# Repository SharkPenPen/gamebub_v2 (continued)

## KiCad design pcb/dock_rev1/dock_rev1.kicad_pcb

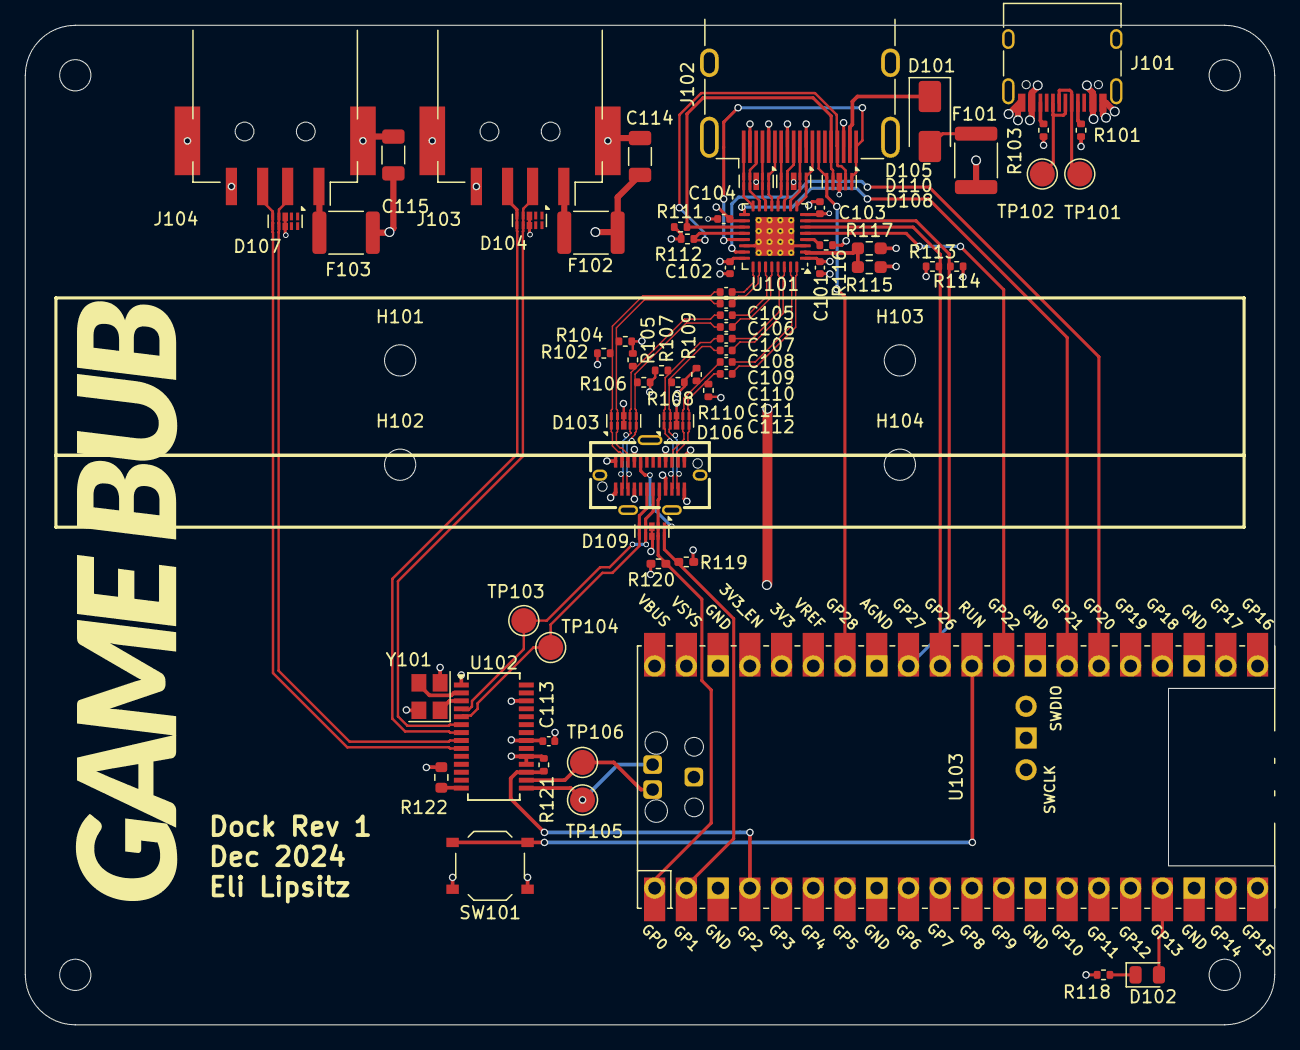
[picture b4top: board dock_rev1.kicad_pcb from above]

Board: 4 copper layers, 100.0 x 80.0 mm, 74 parts (0 on the bottom side), 63 nets.

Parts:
C101, C102, C103, C104, C105, C106, C107, C108, C109, C110, C111, C112, C113: 100n; C_0402_1005Metric
C114, C115: 100u; C_1206_3216Metric
D101: D_Schottky; D_SMA
D102: Green; LED_0805_2012Metric
D103, D104, D105, D106, D107, D108, D109, D110: H5VU25U; Diodes_UDFN-10_1.0x2.5mm_P0.5mm
F101, F102, F103: 500mA; Fuse_1812_4532Metric
H101, H102, H103, H104, H105, H106, H107, H108: MountingHole; MountingHole_2.5mm
J101: USB_C_Receptacle_USB2.0_16P; USB_C_Receptacle_HRO_TYPE-C-31-M-12
J102: HDMI_A; HDMI_A_Molex_208658-1001_Horizontal
J103, J104: USB_A; USB_A_Receptacle_Xunpu_USB-234-BCW
P101: USB_C_Plug; USB-C-SMD_TYPEC-952-ACP24
R101, R103: 5K1; R_0402_1005Metric
R102, R104, R105, R106, R107, R108, R109, R110: 49R9; R_0402_1005Metric
R111, R112, R113, R114, R118: 2K; R_0402_1005Metric
R115, R117: 0R; R_0603_1608Metric_Pad0.98x0.95mm_HandSolder
R116, R121: 10K; R_0402_1005Metric
R119, R120: 2K; R_0402_1005Metric_Pad0.72x0.64mm_HandSolder
R122: 2K7; R_0603_1608Metric
SW101: SW_Push; SW_Push_1P1T_XKB_TS-1187A
TP101, TP102, TP103, TP104, TP105, TP106: TestPoint; TestPoint_Pad_D2.0mm
U101: PTN3365; HVQFN-32-1EP_5x5mm_P0.5mm_EP3.1x3.1mm_ThermalVias
U102: FE1.1s; SSOP-28_3.9x9.9mm_P0.635mm
U103: PicoW; RPi_PicoW_SMD_TH
Y101: 12MHz; Crystal_SMD_3225-4Pin_3.2x2.5mm

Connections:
+3V3: C101.1, C102.1, C103.1, C104.1, C113.1, R102.1, R104.1, R105.1, R106.1, R107.1, R108.1, R109.1, R110.1, R111.1, R112.1, R113.1, R114.1, R115.1, R119.2, R120.2, R121.1, U101.1 (VDD), U101.8 (VDD), U101.18 (VDD), U101.24 (VDD), U102.18 (VBUSM), U102.19 (BUSJ), U102.21 (VD33F), U102.26 (OVCJ), U103.36 (3V3)
/HDMI_+5V_F: D101.2 (A), F101.2
/HDMI_C_CLK+: C111.2, U101.31 (IN_D4−)
/HDMI_C_CLK-: C112.2, U101.32 (IN_D4+)
/HDMI_C_D0+: C109.2, U101.29 (IN_D3−)
/HDMI_C_D0-: C110.2, U101.30 (IN_D3+)
/HDMI_C_D1+: C107.2, U101.27 (IN_D2−)
/HDMI_C_D1-: C108.2, U101.28 (IN_D2+)
/HDMI_C_D2+: C105.2, U101.25 (IN_D1−)
/HDMI_C_D2-: C106.2, U101.26 (IN_D1+)
/HDMI_DDC_EN: U101.23 (DDC_EN), U103.26 (GPIO20)
/HDMI_EQ5: R115.2, R117.1, U101.2 (EQ5)
/HDMI_HPD: U101.5 (HPD_SOURCE), U103.29 (GPIO22)
/HDMI_OUT_+5V: D101.1 (K), J102.18 (+5V)
/HDMI_OUT_CEC: D110.5 (K4), D110.6 (K4), J102.13 (CEC), U103.34 (GPIO28_ADC2)
/HDMI_OUT_CLK+: D108.2 (K2), D108.9 (K2), J102.10 (CK+), U101.10 (OUT_D4−)
/HDMI_OUT_CLK-: D108.1 (K1), D108.10 (K1), J102.12 (CK-), U101.9 (OUT_D4+)
/HDMI_OUT_D0+: D108.5 (K4), D108.6 (K4), J102.7 (D0+), U101.12 (OUT_D3−)
/HDMI_OUT_D0-: D108.4 (K3), D108.7 (K3), J102.9 (D0-), U101.11 (OUT_D3+)
/HDMI_OUT_D1+: D105.2 (K2), D105.9 (K2), J102.4 (D1+), U101.14 (OUT_D2−)
/HDMI_OUT_D1-: D105.1 (K1), D105.10 (K1), J102.6 (D1-), U101.13 (OUT_D2+)
/HDMI_OUT_D2+: D105.5 (K4), D105.6 (K4), J102.1 (D2+), U101.16 (OUT_D1−)
/HDMI_OUT_D2-: D105.4 (K3), D105.7 (K3), J102.3 (D2-), U101.15 (OUT_D1+)
/HDMI_OUT_HPD: D110.1 (K1), D110.10 (K1), J102.19 (HPD), U101.21 (HPD_SINK)
/HDMI_OUT_SCL: D110.4 (K3), D110.7 (K3), J102.15 (SCL), R111.2, U101.19 (SCL_SINK)
/HDMI_OUT_SDA: D110.2 (K2), D110.9 (K2), J102.16 (SDA), R112.2, U101.20 (SDA_SINK)
/HDMI_REXT: R116.2, U101.4 (REXT)
/HDMI_SCL: R114.2, U101.7 (SCL_SOURCE), U103.32 (GPIO27_ADC1)
/HDMI_SDA: R113.2, U101.6 (SDA_SOURCE), U103.31 (GPIO26_ADC0)
/HDMI_TX_CLK+: C111.1, D106.4 (K3), D106.7 (K3), P101.B3 (TX2-), R109.2
/HDMI_TX_CLK-: C112.1, D106.5 (K4), D106.6 (K4), P101.B2 (TX2+), R110.2
/HDMI_TX_D0+: C109.1, D106.1 (K1), D106.10 (K1), P101.A10 (RX2-), R107.2
/HDMI_TX_D0-: C110.1, D106.2 (K2), D106.9 (K2), P101.A11 (RX2+), R108.2
/HDMI_TX_D1+: C107.1, D103.4 (K3), D103.7 (K3), P101.A2 (TX1+), R105.2
/HDMI_TX_D1-: C108.1, D103.5 (K4), D103.6 (K4), P101.A3 (TX1-), R106.2
/HDMI_TX_D2+: C105.1, D103.1 (K1), D103.10 (K1), P101.B11 (RX1+), R102.2
/HDMI_TX_D2-: C106.1, D103.2 (K2), D103.9 (K2), P101.B10 (RX1-), R104.2
/HDMI_~OE: U101.17 (~OE), U103.27 (GPIO21)
/LED: D102.2 (A), U103.17 (GPIO13)
/LED_K: D102.1 (K), R118.1
/MCU_RUN: SW101.2, U103.30 (RUN)
/MCU_USB_D+: TP106.1, U102.16 (DPU), U103.TP3 (USB_D+)
/MCU_USB_D-: TP105.1, U102.15 (DMU), U103.TP2 (USB_D-)
/USB_Device1_D+: D107.5 (K4), D107.6 (K4), J104.3 (D+), U102.9 (DP2)
/USB_Device1_D-: D107.4 (K3), D107.7 (K3), J104.2 (D-), U102.8 (DM2)
/USB_Device2_D+: D104.5 (K4), D104.6 (K4), J103.3 (D+), U102.7 (DP3)
/USB_Device2_D-: D104.4 (K3), D104.7 (K3), J103.2 (D-), U102.6 (DM3)
/USB_Handheld_D+: D109.5 (K4), D109.6 (K4), P101.A6 (D+), TP104.1, U102.5 (DP4)
/USB_Handheld_D-: D109.4 (K3), D109.7 (K3), P101.A7 (D-), TP103.1, U102.4 (DM4)
/USB_Handheld_SBU1: D109.2 (K2), D109.9 (K2), P101.A8 (SBU1), R120.1, U103.1 (GPIO0)
/USB_Handheld_SBU2: D109.1 (K1), D109.10 (K1), P101.B8 (SBU2), R119.1, U103.2 (GPIO1)
/USB_Hub_Rext: R122.2, U102.14 (REXT)
/USB_Hub_XIn: U102.3 (XIN), Y101.1
/USB_Hub_XOut: U102.2 (XOUT), Y101.3
/USB_Power_CC1: J101.A5 (CC1), R101.2
/USB_Power_CC2: J101.B5 (CC2), R103.2
/USB_Power_D+: J101.A6 (D+), J101.B6 (D+), TP102.1
/USB_Power_D-: J101.A7 (D-), J101.B7 (D-), TP101.1
/~USB_Hub_RST: R121.2, U102.17 (~XRSTJ), U103.4 (GPIO2)
GND: C101.2, C102.2, C103.2, C104.2, C113.2, C114.2, C115.2, D103.3 (A), D103.8 (A), D104.3 (A), D104.8 (A), D105.3 (A), D105.8 (A), D106.3 (A), D106.8 (A), D107.3 (A), D107.8 (A), D108.3 (A), D108.8 (A), D109.3 (A), D109.8 (A), D110.3 (A), D110.8 (A), J101.A1 (GND), J101.A12 (GND), J101.B1 (GND), J101.B12 (GND), J101.S1 (SHIELD), J102.2 (D2S), J102.5 (D1S), J102.8 (D0S), J102.11 (CKS), J102.17 (GND), J102.SH, J103.4 (GND), J103.5 (Shield), J104.4 (GND), J104.5 (Shield), P101.A1 (GND), P101.A12 (GND), P101.B1 (GND), P101.B12 (GND), P101.S1 (SHIELD), R101.1, R103.1, R116.1, R117.2, R118.2, R122.1, SW101.1, U101.3 (TEST), U101.22 (GND), U101.33 (GND), U102.1 (VSS), U103.3 (GND), U103.8 (GND), U103.13 (GND), U103.18 (GND), U103.23 (GND), U103.28 (GND), U103.33 (AGND), U103.38 (GND), U103.42 (GND), U103.TP1 (GND), Y101.2, Y101.4
unnamed: F102.1, J103.1 (VBUS)
unnamed: F103.1, J104.1 (VBUS)
VBUS: C114.1, C115.1, F101.1, F102.2, F103.2, J101.A4 (VBUS), J101.A9 (VBUS), J101.B4 (VBUS), J101.B9 (VBUS), P101.A4 (VBUS), P101.A9 (VBUS), P101.B4 (VBUS), P101.B9 (VBUS), U103.39 (VSYS), U103.40 (VBUS)

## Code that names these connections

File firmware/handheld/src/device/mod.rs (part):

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    button_vol_down: PinDriver<'a, AnyInputPin, Input>,
    button_power: PinDriver<'a, AnyIOPin, InputOutput>,
    pin_irq: PinDriver<'a, AnyInputPin, Input>,
    pin_vbus_pgood: PinDriver<'a, AnyIOPin, Input>,
    pin_batt_chg: PinDriver<'a, AnyInputPin, Input>,

    /// Sdcard,
    pub sdcard: Option<Sdcard>,
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        let peripherals = Peripherals::take()?;
        cfg_if::cfg_if! {
            if #[cfg(feature = "rev2")] {
                let pin_led = peripherals.pins.gpio36.downgrade_output();
                let pin_irq = peripherals.pins.gpio16.downgrade_input();
                let pin_home = peripherals.pins.gpio0.downgrade_input();
                let pin_vol_up = peripherals.pins.gpio41.downgrade_input();
                let pin_vol_down = peripherals.pins.gpio40.downgrade_input();
                let pin_power_switch = peripherals.pins.gpio15.downgrade();
                let pin_vbus_pgood = peripherals.pins.gpio17.downgrade();
                let pin_batt_chg = peripherals.pins.gpio39.downgrade_input();
                let pin_lcd_backlight = peripherals.pins.gpio42.downgrade_output();
                let pin_lcd_reset = peripherals.pins.gpio1.downgrade_output();
                let pin_lcd_cs = peripherals.pins.gpio2.downgrade_output();
                let pin_lcd_dc = peripherals.pins.gpio3.downgrade_output();
                let pin_lcd_spi_clk = peripherals.pins.gpio4.downgrade_output();
                let pin_lcd_spi_d0 = peripherals.pins.gpio5.downgrade_output();
                let pin_fpga_power = peripherals.pins.gpio46.downgrade_output();
                let pin_fpga_init_b = peripherals.pins.gpio8.downgrade();
                let pin_fpga_done = peripherals.pins.gpio6.downgrade_input();
                let pin_fpga_program_b = peripherals.pins.gpio7.downgrade_output();
                let mut pin_fpga_spi_cs = peripherals.pins.gpio10.downgrade_output();
                let pin_fpga_spi_clk = peripherals.pins.gpio12.downgrade_output();
                let pin_fpga_spi_d0 = peripherals.pins.gpio11.downgrade();
                let pin_fpga_spi_d1 = peripherals.pins.gpio13.downgrade();
                let pin_fpga_spi_d2 = peripherals.pins.gpio14.downgrade();
                let pin_fpga_spi_d3 = peripherals.pins.gpio9.downgrade();
                let pin_i2c_scl = peripherals.pins.gpio37.downgrade();
                let pin_i2c_sda = peripherals.pins.gpio38.downgrade();
                let pin_sdio_clk = peripherals.pins.gpio33.downgrade_output();
                let pin_sdio_cmd = peripherals.pins.gpio47.downgrade();
                let pin_sdio_d0 = peripherals.pins.gpio34.downgrade();
                let pin_sdio_d1 = peripherals.pins.gpio48.downgrade();
                let pin_sdio_d2 = peripherals.pins.gpio21.downgrade();
                let pin_sdio_d3 = peripherals.pins.gpio26.downgrade();
                let pin_sd_detect = peripherals.pins.gpio35.downgrade_input();
                let pin_dac_reset = peripherals.pins.gpio45.downgrade_output();
            }
        }

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                    .frequency(25.kHz().into())
                    .resolution(ledc::config::Resolution::Bits11),
            )?,
            pin_lcd_backlight,
        )?;
        lcd_backlight.set_duty_cycle_fully_off().unwrap();

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            if #[cfg(feature = "rev2")] {
                let fpga_spi_driver = &*Box::leak(Box::new(SpiDriver::new_quad(
                    peripherals.spi2,
                    pin_fpga_spi_clk,
                    pin_fpga_spi_d0,
                    pin_fpga_spi_d1,
                    pin_fpga_spi_d2,
                    pin_fpga_spi_d3,
                    &spi_driver_config,
                )?));
                let lcd_spi_driver = &*Box::leak(Box::new(SpiDriver::new(
                    peripherals.spi3,
                    pin_lcd_spi_clk,
                    pin_lcd_spi_d0,
                    Option::<AnyInputPin>::None,
                    &spi_driver_config,
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        let lcd_spi_config = spi::config::Config::new().baudrate(10.MHz().into());
        let lcd_spi = SpiSoftCsDeviceDriver::new(
            SpiSharedDeviceDriver::new(lcd_spi_driver, &lcd_spi_config)?,
            pin_lcd_cs,
            gpio::Level::High,
        )?;
        let lcd_reset = PinDriver::output(pin_lcd_reset)?;
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        // Setup battery fuel gauge
        let mut fuel_gauge = drivers::fuel_gauge::MAX17048::new(MutexI2C::new(&i2c));
        let _ = fuel_gauge.set_alert_soc_change(true); // fuel gauge won't work without a battery
        let mut pin_vbus_pgood = PinDriver::input(pin_vbus_pgood)?;
        pin_vbus_pgood.set_pull(gpio::Pull::Up)?;
        let pin_batt_chg = PinDriver::input(pin_batt_chg)?;

        // Low-voltage interlock: never bring the FPGA up on a collapsing rail.
        // The FPGA is simply left unpowered and the boot continues, so the
        // self-test can still report why the device is not starting.
        let vbus_present = pin_vbus_pgood.is_low(); // Active low
        match fuel_gauge.get_battery_voltage() {
            Ok(voltage) if crate::power::is_battery_critical(voltage, vbus_present) => {
                log::error!(
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
        // Setup DAC (requires fpga_power on)
        log::info!("Initializing DAC");
        let dac_reset = PinDriver::output(pin_dac_reset)?;
        let mut dac = drivers::dac::TLV320DAC3101::new(dac_reset, MutexI2C::new(&i2c));
        // The DAC shares the I2C bus and sits on the FPGA power domain, so a
        // failure here must not stop the boot.
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        }

        // Setup FPGA (without programming)
        let fpga_done = PinDriver::input(pin_fpga_done)?;
        let mut fpga_program_b = PinDriver::output_od(pin_fpga_program_b)?;
        fpga_program_b.set_high()?; // Initializing pin sets this to low -- release it to high-z immediately.
        let fpga_init_b = PinDriver::input(pin_fpga_init_b)?;

        let spi_rates = [40.MHz(), 20.MHz(), 16.MHz(), 10.MHz()];
        let fpga_data_spis = spi_rates
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                // They're used in the same mode (output), and controlled only by software,
                // and never used at the same time (either read *or* write are used at any time).
                // There doesn't appear to be any other way to use multiple clock speeds.
                let cs_pin = unsafe { pin_fpga_spi_cs.clone_unchecked() };
                let mut spi = SpiSoftCsDeviceDriver::new(
                    SpiSharedDeviceDriver::new(fpga_spi_driver, &config).unwrap(),
                    cs_pin,
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        // Mount sdcard to /sdcard
        let sdcard = drivers::sdcard::mount_sdcard(
            "/sdcard",
            pin_sdio_clk,
            pin_sdio_cmd,
            pin_sdio_d0,
            pin_sdio_d1,
            pin_sdio_d2,
            pin_sdio_d3,
            Some(pin_sd_detect),
        )
        .ok();

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            button_vol_up,
            button_vol_down,
            pin_irq,
            pin_batt_chg,
            pin_vbus_pgood,
            rtc,
            imu,
            sdcard,
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    }

    pub fn get_battery_is_charging(&self) -> bool {
        self.pin_batt_chg.is_high()
    }

    pub fn get_vbus_pgood(&self) -> bool {
        self.pin_vbus_pgood.is_low() // Active low
    }
}

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
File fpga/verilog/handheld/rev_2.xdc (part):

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########################################
# Link Port
########################################
set_property -dict { PACKAGE_PIN C1     IOSTANDARD LVCMOS33 } [get_ports { link_so     }];
set_property -dict { PACKAGE_PIN D2     IOSTANDARD LVCMOS33 } [get_ports { link_si     }];
set_property -dict { PACKAGE_PIN E2     IOSTANDARD LVCMOS33 } [get_ports { link_sd     }];
set_property -dict { PACKAGE_PIN G2     IOSTANDARD LVCMOS33 } [get_ports { link_sc     }];
set_property -dict { PACKAGE_PIN C2     IOSTANDARD LVCMOS33 } [get_ports { link_so_dir }];
set_property -dict { PACKAGE_PIN E1     IOSTANDARD LVCMOS33 } [get_ports { link_si_dir }];
set_property -dict { PACKAGE_PIN F1     IOSTANDARD LVCMOS33 } [get_ports { link_sd_dir }];
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########################################
# LCD
########################################
set_property -dict { PACKAGE_PIN E17    IOSTANDARD LVCMOS33 } [get_ports { lcd_dotclk  }];
set_property -dict { PACKAGE_PIN E18    IOSTANDARD LVCMOS33 } [get_ports { lcd_hsync   }];
set_property -dict { PACKAGE_PIN D17    IOSTANDARD LVCMOS33 } [get_ports { lcd_vsync   }];
set_property -dict { PACKAGE_PIN F18    IOSTANDARD LVCMOS33 } [get_ports { lcd_data_en }];
set_property -dict { PACKAGE_PIN T11    IOSTANDARD LVCMOS33 } [get_ports { lcd_te      }];
set_property -dict { PACKAGE_PIN K16    IOSTANDARD LVCMOS33 } [get_ports { lcd_db[0]   }];
set_property -dict { PACKAGE_PIN K15    IOSTANDARD LVCMOS33 } [get_ports { lcd_db[1]   }];
set_property -dict { PACKAGE_PIN J15    IOSTANDARD LVCMOS33 } [get_ports { lcd_db[2]   }];
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########################################
# Buttons
########################################
set_property -dict { PACKAGE_PIN N5     IOSTANDARD LVCMOS33 } [get_ports { btn_a      }];
set_property -dict { PACKAGE_PIN P5     IOSTANDARD LVCMOS33 } [get_ports { btn_b      }];
set_property -dict { PACKAGE_PIN L6     IOSTANDARD LVCMOS33 } [get_ports { btn_x      }];
set_property -dict { PACKAGE_PIN M6     IOSTANDARD LVCMOS33 } [get_ports { btn_y      }];
set_property -dict { PACKAGE_PIN E5     IOSTANDARD LVCMOS33 } [get_ports { btn_up     }];
set_property -dict { PACKAGE_PIN H5     IOSTANDARD LVCMOS33 } [get_ports { btn_down   }];
set_property -dict { PACKAGE_PIN G6     IOSTANDARD LVCMOS33 } [get_ports { btn_left   }];
set_property -dict { PACKAGE_PIN F5     IOSTANDARD LVCMOS33 } [get_ports { btn_right  }];
set_property -dict { PACKAGE_PIN E6     IOSTANDARD LVCMOS33 } [get_ports { btn_l      }];
set_property -dict { PACKAGE_PIN L5     IOSTANDARD LVCMOS33 } [get_ports { btn_r      }];
set_property -dict { PACKAGE_PIN K5     IOSTANDARD LVCMOS33 } [get_ports { btn_start  }];
set_property -dict { PACKAGE_PIN J5     IOSTANDARD LVCMOS33 } [get_ports { btn_select }];

########################################
# DAC I2S
########################################
set_property -dict { PACKAGE_PIN G4     IOSTANDARD LVCMOS33 } [get_ports { dac_mclk }];
set_property -dict { PACKAGE_PIN H4     IOSTANDARD LVCMOS33 } [get_ports { dac_wclk }];
set_property -dict { PACKAGE_PIN G3     IOSTANDARD LVCMOS33 } [get_ports { dac_bclk }];
set_property -dict { PACKAGE_PIN J4     IOSTANDARD LVCMOS33 } [get_ports { dac_din  }];

########################################
# MCU Communication
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set_property -dict { PACKAGE_PIN A18    IOSTANDARD TMDS_33  } [get_ports { hdmi_data_p[2] }];
set_property -dict { PACKAGE_PIN B18    IOSTANDARD TMDS_33  } [get_ports { hdmi_data_n[2] }];

set_property -dict { PACKAGE_PIN F3     IOSTANDARD LVCMOS33 } [get_ports { usb_sbu_1 }];
set_property -dict { PACKAGE_PIN D3     IOSTANDARD LVCMOS33 } [get_ports { usb_sbu_2 }];

########################################
# Vibration
########################################
set_property -dict { PACKAGE_PIN B1     IOSTANDARD LVCMOS33 } [get_ports { vibrate_en    }];
set_property -dict { PACKAGE_PIN A1     IOSTANDARD LVCMOS33 } [get_ports { vibrate_brake }];

########################################
# PMOD
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set_property -dict { PACKAGE_PIN N4     IOSTANDARD LVCMOS33 } [get_ports { sdram_bs[0] }];
set_property -dict { PACKAGE_PIN P3     IOSTANDARD LVCMOS33 } [get_ports { sdram_bs[1] }];

set_property -dict { PACKAGE_PIN V4     IOSTANDARD LVCMOS33 } [get_ports { sdram_clk   }];
set_property -dict { PACKAGE_PIN R2     IOSTANDARD LVCMOS33 } [get_ports { sdram_we_n  }];
set_property -dict { PACKAGE_PIN R1     IOSTANDARD LVCMOS33 } [get_ports { sdram_ldqm  }];
set_property -dict { PACKAGE_PIN T5     IOSTANDARD LVCMOS33 } [get_ports { sdram_udqm  }];
set_property -dict { PACKAGE_PIN T1     IOSTANDARD LVCMOS33 } [get_ports { sdram_cas_n }];
set_property -dict { PACKAGE_PIN U1     IOSTANDARD LVCMOS33 } [get_ports { sdram_ras_n }];
set_property -dict { PACKAGE_PIN U4     IOSTANDARD LVCMOS33 } [get_ports { sdram_cke   }];
set_property -dict { PACKAGE_PIN V1     IOSTANDARD LVCMOS33 } [get_ports { sdram_cs_n  }];

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
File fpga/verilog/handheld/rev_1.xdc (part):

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########################################
# Link Port
########################################
set_property -dict { PACKAGE_PIN L13    IOSTANDARD LVCMOS33 } [get_ports { link_so     }];
set_property -dict { PACKAGE_PIN J14    IOSTANDARD LVCMOS33 } [get_ports { link_si     }];
set_property -dict { PACKAGE_PIN F14    IOSTANDARD LVCMOS33 } [get_ports { link_sd     }];
set_property -dict { PACKAGE_PIN G13    IOSTANDARD LVCMOS33 } [get_ports { link_sc     }];
set_property -dict { PACKAGE_PIN L14    IOSTANDARD LVCMOS33 } [get_ports { link_so_dir }];
set_property -dict { PACKAGE_PIN H14    IOSTANDARD LVCMOS33 } [get_ports { link_si_dir }];
set_property -dict { PACKAGE_PIN F13    IOSTANDARD LVCMOS33 } [get_ports { link_sd_dir }];
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########################################
# LCD
########################################
set_property -dict { PACKAGE_PIN E17    IOSTANDARD LVCMOS33 } [get_ports { lcd_dotclk  }];
set_property -dict { PACKAGE_PIN E18    IOSTANDARD LVCMOS33 } [get_ports { lcd_hsync   }];
set_property -dict { PACKAGE_PIN D17    IOSTANDARD LVCMOS33 } [get_ports { lcd_vsync   }];
set_property -dict { PACKAGE_PIN F18    IOSTANDARD LVCMOS33 } [get_ports { lcd_data_en }];
set_property -dict { PACKAGE_PIN K16    IOSTANDARD LVCMOS33 } [get_ports { lcd_db[0]   }];
set_property -dict { PACKAGE_PIN K15    IOSTANDARD LVCMOS33 } [get_ports { lcd_db[1]   }];
set_property -dict { PACKAGE_PIN J15    IOSTANDARD LVCMOS33 } [get_ports { lcd_db[2]   }];
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########################################
# Buttons
########################################
set_property -dict { PACKAGE_PIN N5     IOSTANDARD LVCMOS33 } [get_ports { btn_a      }];
set_property -dict { PACKAGE_PIN P5     IOSTANDARD LVCMOS33 } [get_ports { btn_b      }];
set_property -dict { PACKAGE_PIN L6     IOSTANDARD LVCMOS33 } [get_ports { btn_x      }];
set_property -dict { PACKAGE_PIN M6     IOSTANDARD LVCMOS33 } [get_ports { btn_y      }];
set_property -dict { PACKAGE_PIN E5     IOSTANDARD LVCMOS33 } [get_ports { btn_up     }];
set_property -dict { PACKAGE_PIN H5     IOSTANDARD LVCMOS33 } [get_ports { btn_down   }];
set_property -dict { PACKAGE_PIN G6     IOSTANDARD LVCMOS33 } [get_ports { btn_left   }];
set_property -dict { PACKAGE_PIN F5     IOSTANDARD LVCMOS33 } [get_ports { btn_right  }];
set_property -dict { PACKAGE_PIN H6     IOSTANDARD LVCMOS33 } [get_ports { btn_l      }];
set_property -dict { PACKAGE_PIN L5     IOSTANDARD LVCMOS33 } [get_ports { btn_r      }];
set_property -dict { PACKAGE_PIN K5     IOSTANDARD LVCMOS33 } [get_ports { btn_start  }];
set_property -dict { PACKAGE_PIN J5     IOSTANDARD LVCMOS33 } [get_ports { btn_select }];

########################################
# DAC I2S
########################################
set_property -dict { PACKAGE_PIN G4     IOSTANDARD LVCMOS33 } [get_ports { dac_mclk }];
set_property -dict { PACKAGE_PIN H4     IOSTANDARD LVCMOS33 } [get_ports { dac_wclk }];
set_property -dict { PACKAGE_PIN G3     IOSTANDARD LVCMOS33 } [get_ports { dac_bclk }];
set_property -dict { PACKAGE_PIN J4     IOSTANDARD LVCMOS33 } [get_ports { dac_din  }];

########################################
# MCU Communication
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set_property -dict { PACKAGE_PIN F1     IOSTANDARD TMDS_33  } [get_ports { hdmi_data_p[2] }];
set_property -dict { PACKAGE_PIN E1     IOSTANDARD TMDS_33  } [get_ports { hdmi_data_n[2] }];

# set_property -dict { PACKAGE_PIN D3     IOSTANDARD LVCMOS33 } [get_ports { hdmi_scl   }];
# set_property -dict { PACKAGE_PIN E6     IOSTANDARD LVCMOS33 } [get_ports { hdmi_sda   }];
# set_property -dict { PACKAGE_PIN F3     IOSTANDARD LVCMOS33 } [get_ports { hdmi_hpd_n }];
# set_property -dict { PACKAGE_PIN F6     IOSTANDARD LVCMOS33 } [get_ports { hdmi_cec   }];

########################################
# Vibration
########################################
set_property -dict { PACKAGE_PIN E7     IOSTANDARD LVCMOS33 } [get_ports { vibrate_en }];

########################################
# PMOD
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set_property -dict { PACKAGE_PIN N4     IOSTANDARD LVCMOS33 } [get_ports { sdram_bs[0] }];
set_property -dict { PACKAGE_PIN P3     IOSTANDARD LVCMOS33 } [get_ports { sdram_bs[1] }];

set_property -dict { PACKAGE_PIN V4     IOSTANDARD LVCMOS33 } [get_ports { sdram_clk   }];
set_property -dict { PACKAGE_PIN R2     IOSTANDARD LVCMOS33 } [get_ports { sdram_we_n  }];
set_property -dict { PACKAGE_PIN R1     IOSTANDARD LVCMOS33 } [get_ports { sdram_ldqm  }];
set_property -dict { PACKAGE_PIN T5     IOSTANDARD LVCMOS33 } [get_ports { sdram_udqm  }];
set_property -dict { PACKAGE_PIN T1     IOSTANDARD LVCMOS33 } [get_ports { sdram_cas_n }];
set_property -dict { PACKAGE_PIN U1     IOSTANDARD LVCMOS33 } [get_ports { sdram_ras_n }];
set_property -dict { PACKAGE_PIN U4     IOSTANDARD LVCMOS33 } [get_ports { sdram_cke   }];
set_property -dict { PACKAGE_PIN V1     IOSTANDARD LVCMOS33 } [get_ports { sdram_cs_n  }];

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
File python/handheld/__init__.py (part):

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from .fpga import FPGA
from .tca9535 import TCA9535

pin_btn_home = Pin(0, Pin.IN)
pin_power_switch_n = Pin(1, Pin.IN)  # in/out
mcu_irq = Pin(2, Pin.IN)
status_led = Pin(3, Pin.OUT)
pin_btn_vol_up = Pin(4, Pin.IN)
pin_btn_vol_down = Pin(5, Pin.IN)
lcd_backlight = Pin(6, Pin.OUT)
lcd_reset = Pin(7, Pin.OUT)
lcd_cs = Pin(15, Pin.OUT)
lcd_dc = Pin(16, Pin.OUT)
dac_reset = Pin(40, Pin.OUT)
fpga_power = Pin(46, Pin.OUT)
fpga_done = Pin(17, Pin.IN)
fpga_program_b = Pin(18, Pin.OPEN_DRAIN, value=1)
fpga_init_b = Pin(8, Pin.IN)
fpga_spi_cs = Pin(10, Pin.OUT)
pin_vbus_pgood_n = Pin(41, Pin.IN)
pin_batt_chg = Pin(42, Pin.IN)
pin_sd_detect = Pin(37, Pin.IN)

pin_btn_home.irq(handler = lambda _: print("IRQ: home"))
pin_power_switch_n.irq(handler = lambda _: print("IRQ: power"))

# BUG (Rev A): FPGA can interfere with LCD SPI, also using LCD SPI while FPGA is unpowered probably isn't great
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i2c.writeto_mem(0x6A, 0x12, b"\x00\x10")

print("Initializing LCD")
lcd = ILI9488(lambda: spi(10_000_000), pin_rst=lcd_reset, pin_cs=lcd_cs, pin_dc=lcd_dc)
lcd.setup()

print("Initializing DAC")
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    # TODO improve
    global dac
    global audio_muted
    if pin is pin_btn_vol_down:
        print("IRQ: volume down", pin_btn_vol_down.value())
        if pin_btn_vol_down.value() == 0:
            dac.set_speakers_enabled(audio_muted)
            audio_muted = not audio_muted
            print("Toggling speaker mute: ", audio_muted)
    if pin is pin_btn_vol_up:
        print("IRQ: volume up", pin_btn_vol_up.value())

pin_btn_vol_up.irq(handler = volume_btn_handler)
pin_btn_vol_down.irq(handler = volume_btn_handler)

print("Initializing MCU IRQ")
def irq_handler(_pin):
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        print("ERROR: nIRQ is still low!")

    # TODO others...
mcu_irq.irq(handler = irq_handler, trigger = Pin.IRQ_FALLING)

print("Passing control of display to FPGA")
# BPGRAM=0 (write to mem), RM=1 (RGB interface), DM=1 (DOTCLK), RCM=0 (DE mode), 
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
